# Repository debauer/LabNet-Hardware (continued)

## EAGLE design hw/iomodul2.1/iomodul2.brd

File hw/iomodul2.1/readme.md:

# Node V2.1

### V2.0 10'14 artwork by  
Sarah, Fablab KA  
Florolf, Entropia KA  

### V2.1 03'15 mod by
David Bauer, FabLab KA

- Hühnerfutter size changed from 0604 to 0805
- added and moved the LEDs
- changed JTAG/SWD connector layout to fit ti the STM SWD

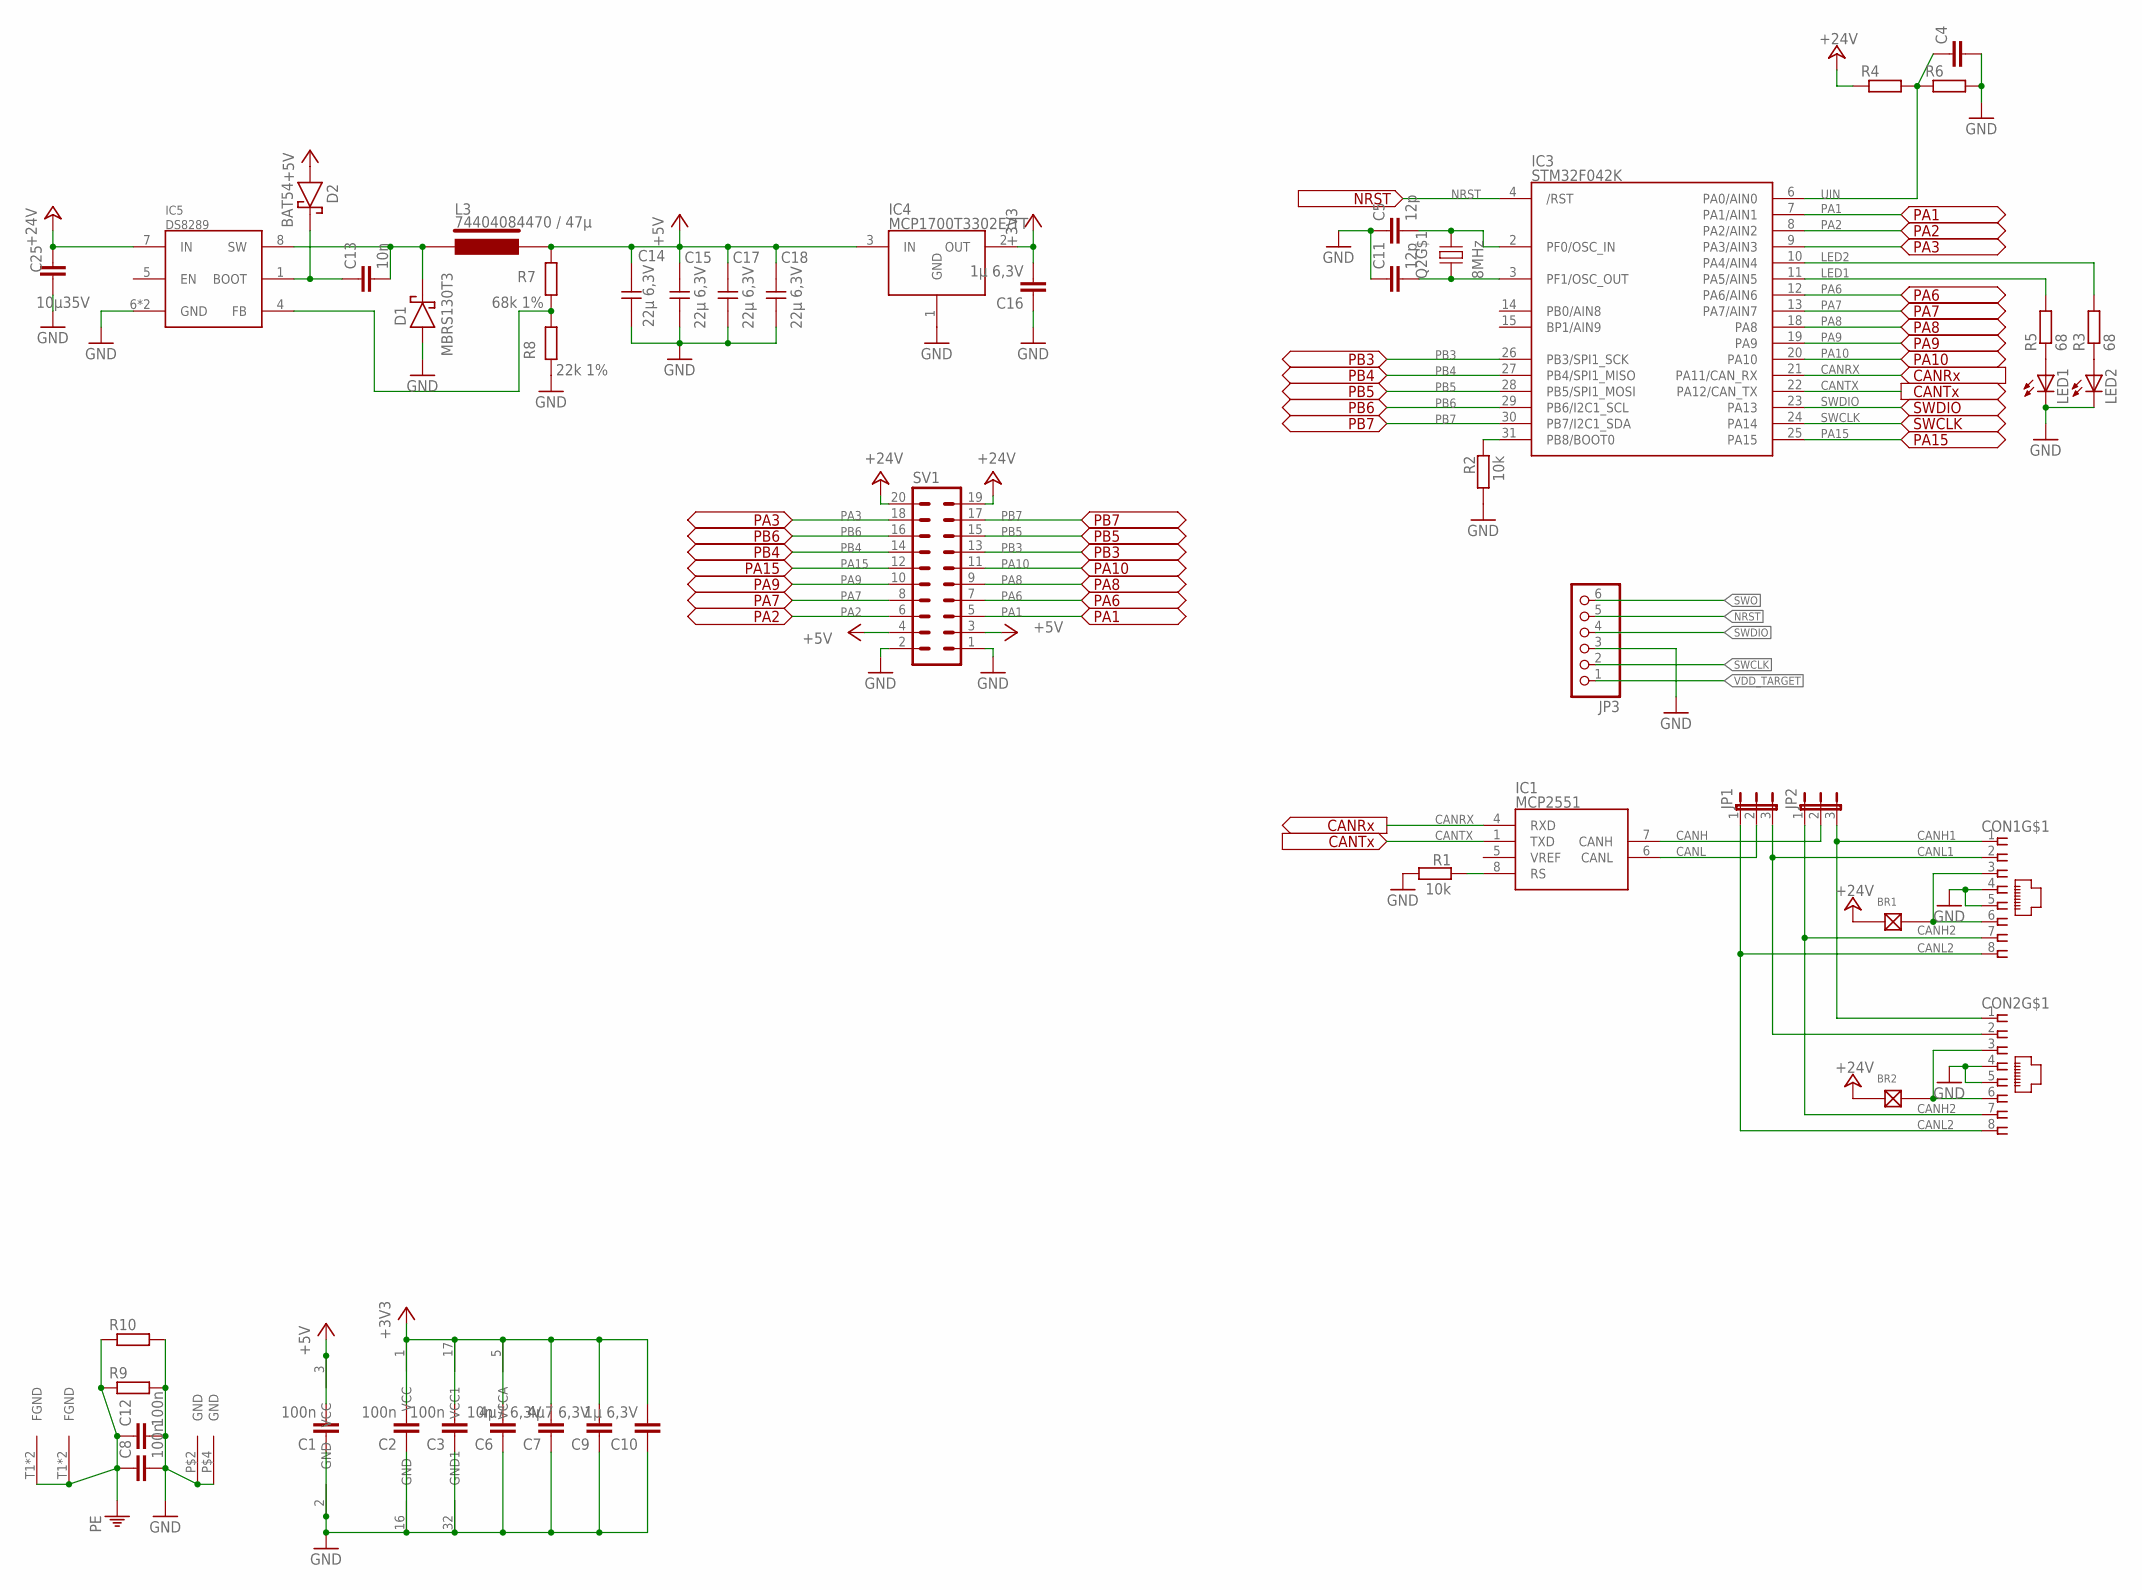
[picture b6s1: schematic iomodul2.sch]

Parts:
BR1, BR2: LÖTBRÜCKE-S; LÖTBRÜCKE
C1, C2, C3, C8, C12: 100n; C1206
C4: C-EUC1206; C1206
C5, C11: 12p; C1206
C6, C13: 10n; C1206
C7, C9: 4µ7 6,3V; C1206
C10, C16: 1µ 6,3V; C1206
C14, C15, C17, C18: 22µ 6,3V; 1210
C25: 10µ35V; C1206
CON1, CON2: MEBP_8-8G; MEBP
D1: MBRS130T3; SMB
D2: BAT54; SOT23/32
IC1: MCP2551; SO-8
IC3: STM32F042K; LQFP32
IC4: MCP1700T3302E/TT; SOT23
IC5: DS8289; SO8-POWERPAD
JP1, JP2: JP2E; JP2
JP3: PINHD-1X6; 1X06
L3: 74404084470 / 47µ; WE-LQS
LED1, LED2: LEDCHIPLED_0603; CHIPLED_0603
Q2: 8MHz; MT-CRYSTAL
R1, R2: 10k; R1206
R3, R5: 68; R1206
R4, R6, R9, R10: R-EU_R1206; R1206
R7: 68k 1%; R1206
R8: 22k 1%; R1206
SV1: MA10-2

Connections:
+3V3: C2.2, C3.2, C6.2, C7.2, C9.2, C10.2, C16.2, IC3.1 (VCC), IC3.5 (VCCA), IC3.17 (VCC1), IC4.2 (OUT)
+5V: C1.2, C14.2, C15.2, C17.2, C18.2, D2.1 (A), IC1.3 (VCC), IC4.3 (IN), L3.P$2, R7.2, SV1.3, SV1.4
+24V: BR1.1, BR2.1, C25.2, IC5.7 (IN), R4.1, SV1.19, SV1.20
CANH: IC1.7 (CANH), JP2.2
CANH1: CON1.1, CON2.1, JP2.3
CANH2: CON1.7, CON2.7, JP2.1
CANL: IC1.6 (CANL), JP1.2
CANL1: CON1.2, CON2.2, JP1.3
CANL2: CON1.8, CON2.8, JP1.1
CANRX: IC1.4 (RXD), IC3.21 (PA11/CAN_RX)
CANTX: IC1.1 (TXD), IC3.22 (PA12/CAN_TX)
GND: C1.1, C2.1, C3.1, C4.2, C5.1, C6.1, C7.1, C8.2, C9.1, C10.1, C11.1, C12.2, C14.1, C15.1, C16.1, C17.1, C18.1, C25.1, CON1.4, CON1.5, CON2.4, CON2.5, D1.A, IC1.2 (GND), IC3.16 (GND), IC3.32 (GND1), IC4.1 (GND), IC5.6 (GND), IC5.TP (GND), JP3.3, LED1.C, LED2.C, Q2.P$2 (GND), Q2.P$4 (GND), R1.2, R2.2, R6.2, R8.1, R9.2, R10.2, SV1.1, SV1.2
LED1: IC3.11 (PA5/AIN5), R5.2
LED2: IC3.10 (PA4/AIN4), R3.2
unnamed: IC1.8 (RS), R1.1
unnamed: BR1.2, CON1.3, CON1.6
unnamed: LED2.A, R3.1
unnamed: C11.2, IC3.3 (PF1/OSC_OUT), Q2.P$1 (1)
unnamed: C5.2, IC3.2 (PF0/OSC_IN), Q2.P$3 (2)
unnamed: BR2.2, CON2.3, CON2.6
unnamed: LED1.A, R5.1
unnamed: C13.1, D2.3 (K), IC5.1 (BOOT)
unnamed: C13.2, D1.K, IC5.8 (SW), L3.P$1
unnamed: IC3.31 (PB8/BOOT0), R2.1
unnamed: IC5.4 (FB), R7.1, R8.2
NRST: IC3.4 (/RST), JP3.5
PA1: IC3.7 (PA1/AIN1), SV1.5
PA2: IC3.8 (PA2/AIN2), SV1.6
PA3: IC3.9 (PA3/AIN3), SV1.18
PA6: IC3.12 (PA6/AIN6), SV1.7
PA7: IC3.13 (PA7/AIN7), SV1.8
PA8: IC3.18 (PA8), SV1.9
PA9: IC3.19 (PA9), SV1.10
PA10: IC3.20 (PA10), SV1.11
PA15: IC3.25 (PA15), SV1.12
PB3: IC3.26 (PB3/SPI1_SCK), SV1.13
PB4: IC3.27 (PB4/SPI1_MISO), SV1.14
PB5: IC3.28 (PB5/SPI1_MOSI), SV1.15
PB6: IC3.29 (PB6/I2C1_SCL), SV1.16
PB7: IC3.30 (PB7/I2C1_SDA), SV1.17
PE: C8.1, C12.1, CON1.T1 (FGND), CON1.T2 (FGND), CON2.T1 (FGND), CON2.T2 (FGND), R9.1, R10.1
SWCLK: IC3.24 (PA14), JP3.2
SWDIO: IC3.23 (PA13), JP3.4
SWO: JP3.6
UIN: C4.1, IC3.6 (PA0/AIN0), R4.2, R6.1
VDD_TARGET: JP3.1

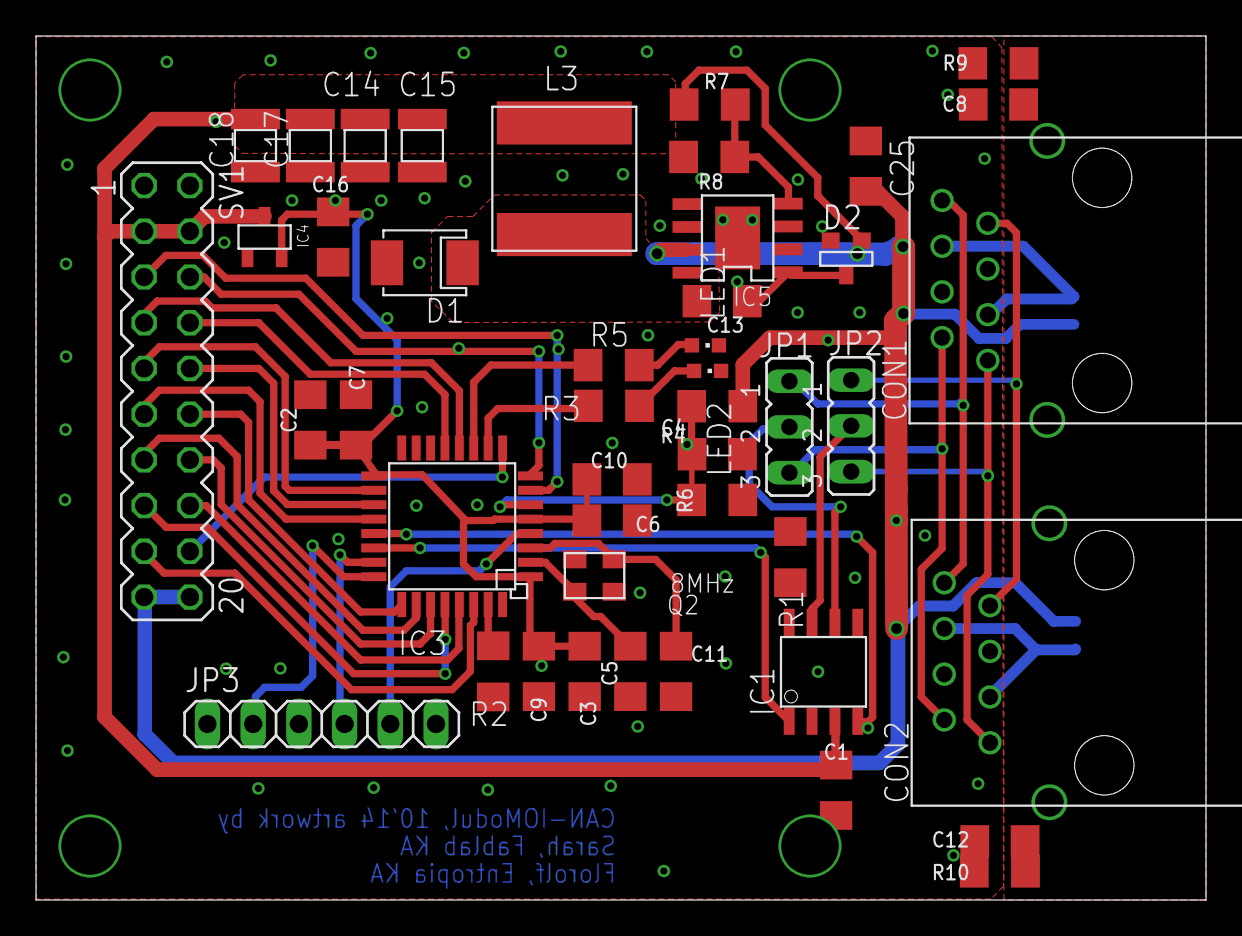
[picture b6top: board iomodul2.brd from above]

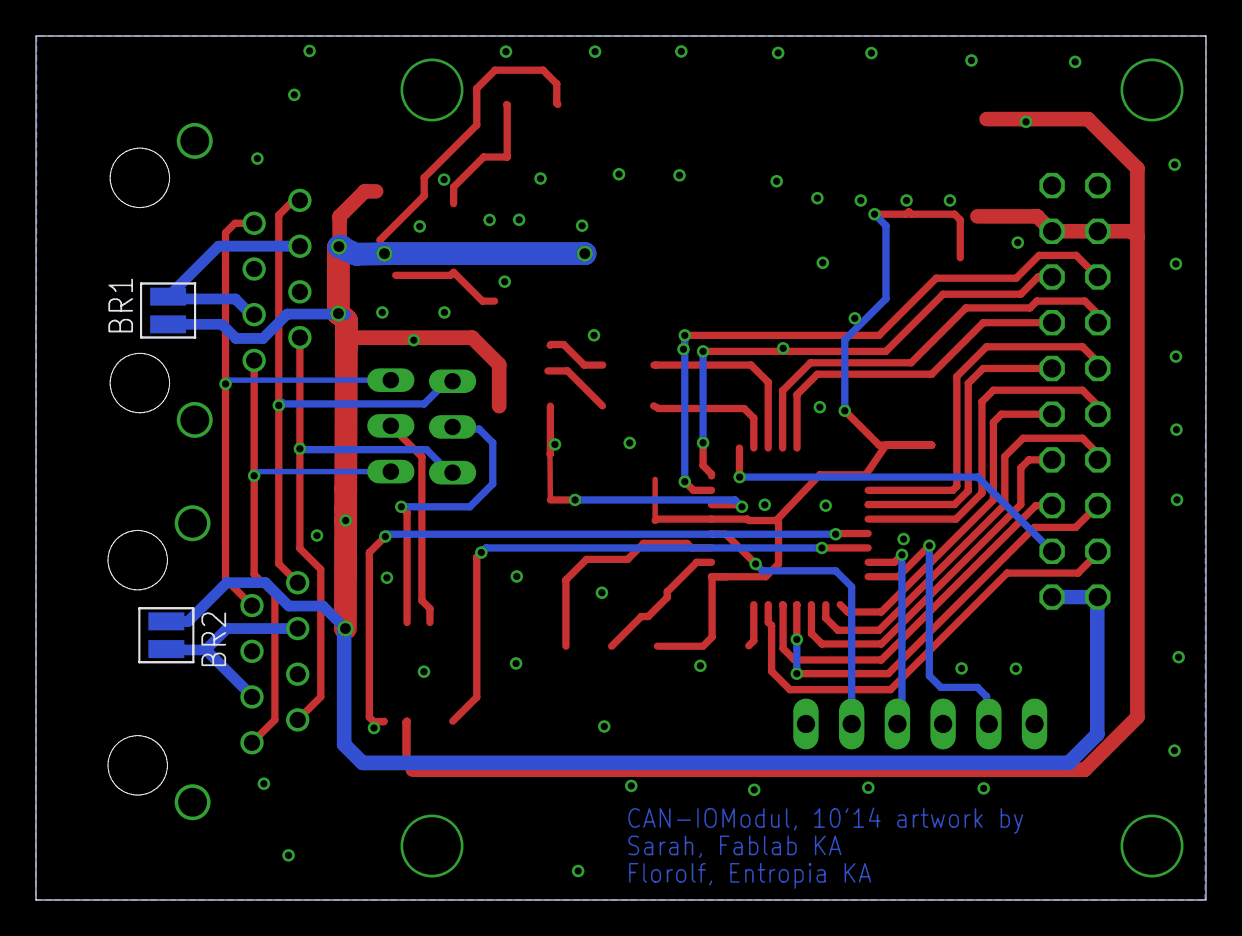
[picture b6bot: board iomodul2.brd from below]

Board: 2 copper layers, 65.0 x 48.0 mm, 47 parts (2 on the bottom side), 44 nets.

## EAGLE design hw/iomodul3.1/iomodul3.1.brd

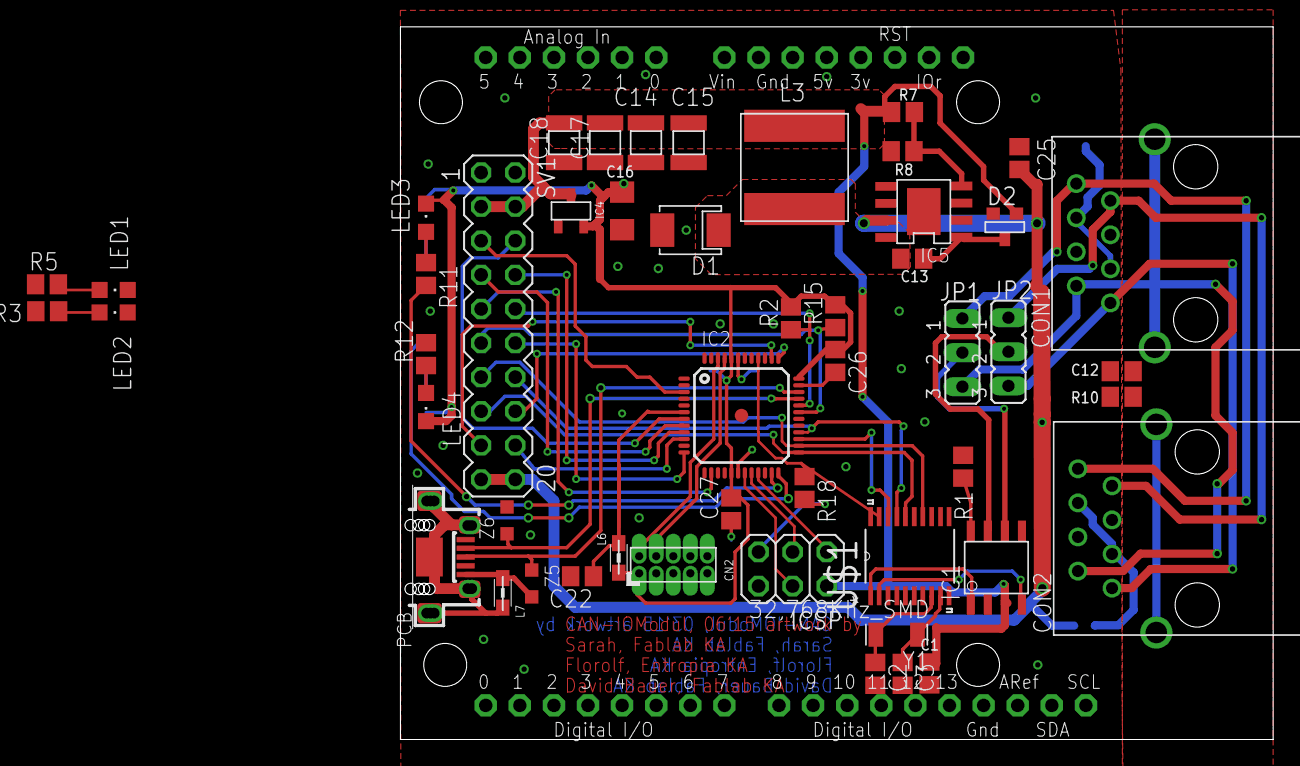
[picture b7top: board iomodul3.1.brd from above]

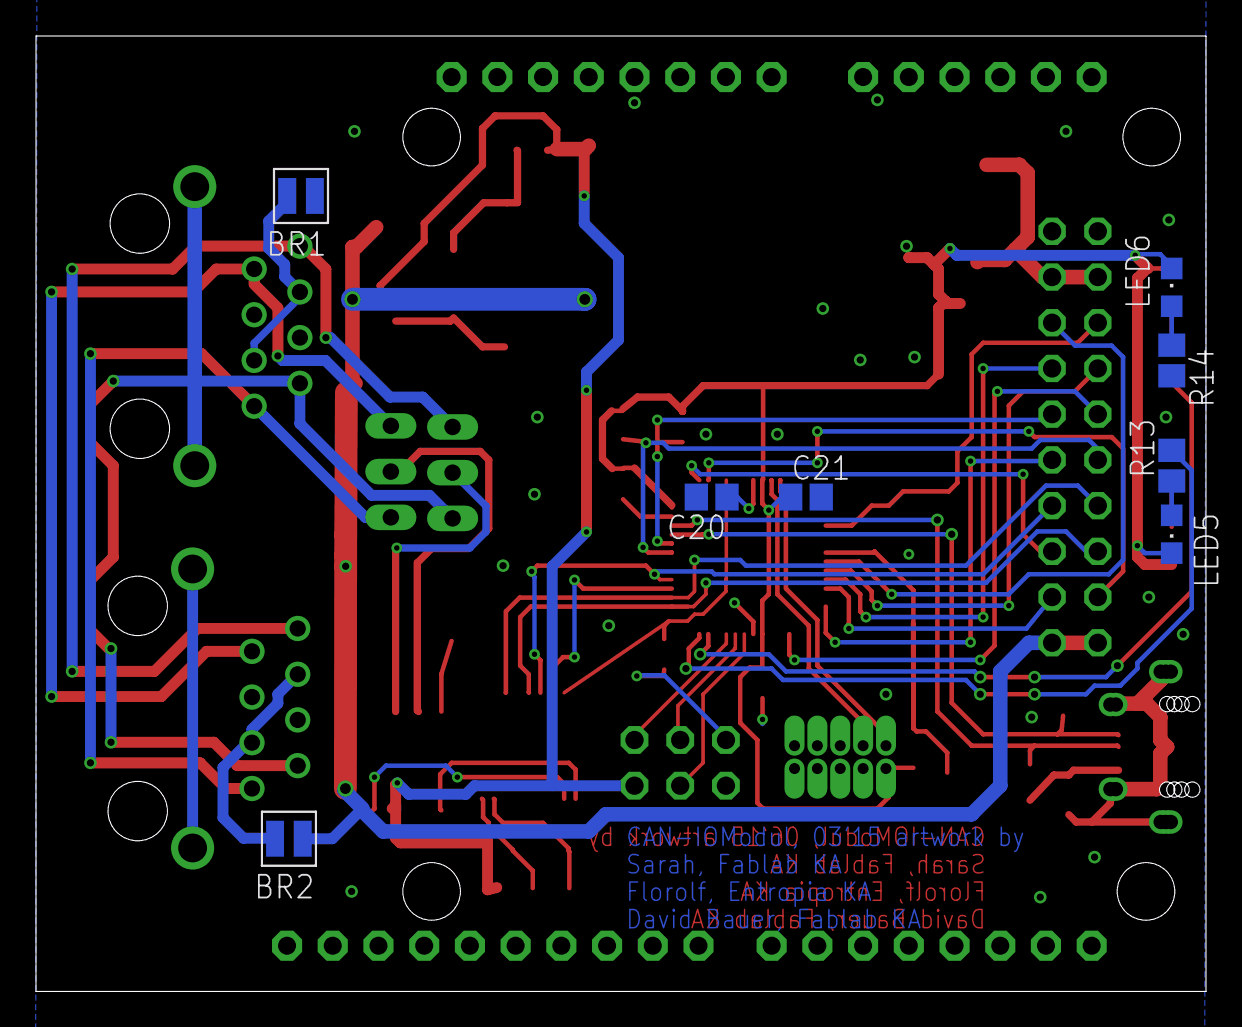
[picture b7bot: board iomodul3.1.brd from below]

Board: 2 copper layers, 65.0 x 53.1 mm, 59 parts (8 on the bottom side), 56 nets.

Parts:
BR1, BR2: LÖTBRÜCKE-S; LÖTBRÜCKE
C1, C12: 100n; C0805
C2, C3: 22p; C0805
C13: 10n; C0805
C14, C15, C17, C18: 22µ 6,3V; 1210
C16: 1µ 6,3V; C1206
C20: 1uF; C0805
C21, C22, C26, C27: 100nF; C0805
C25: 10µ35V; C0805
CN2: PINHEAD-2x5-P1.27; PINHEAD-2X5-P127
CON1, CON2: MEBP
D1: MBRS130T3; SMB
D2: BAT54; SOT23/32
IC1: MCP2551; SO-8
IC2: SAMD21G18A-AUT; TQFP48-7X7
IC4: MCP1700T3302E/TT; SOT23
IC5: DS8289; SO8-POWERPAD
ICSP: 3x2 M; 2X03
JP1, JP2: JP2
L3: 74404084470 / 47µ; WE-LQS
L6, L7: MH2029-300Y; 0805
LED1, LED2, LED3, LED4, LED5, LED6: CHIPLED_0805
R1, R2, R15: 10k; R0805
R3, R5, R11, R12, R13, R14: 68; R0805
R7: 68k 1%; R0805
R8: 22k 1%; R0805
R10: R0805
R18: 330R; R0805
SV1: MA10-2
U1: ARDUINOR3-DIMENSION; ARDUINOR3
U$1: MCP2515-I/ST; SOP65P640X110-20N
USB2: MICRO-USB-AB1; MCR-AB1-S-RA-SMT
Y1: 32,768Khz_SMD; RESONATOR_EPSON_FC_145
Z5, Z6: CG0603MLC-05E; CT/CN0603

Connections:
#0_RX: IC2.38, SV1.17, U1.D0
#1_TX: IC2.37, SV1.16, U1.D1
#3_IO: IC2.14, SV1.9
#5_LED1: IC2.24, R12.2, R13.2
#6_LED2: IC2.23, R11.2, R14.2
#9_CS_HEADER: IC2.12, SV1.12, U1.D9
#11_MOSI: IC2.25, SV1.15, U1.D11, U$1.16
#12_MISO: IC2.28, SV1.14, U1.D12, U$1.17
#13_SCK: IC2.26, SV1.13, U1.D10, U1.D13, U$1.14
#A0: IC2.3, SV1.5, U1.A0
#A1: IC2.7, SV1.6, U1.A1
#A2: IC2.8, SV1.7, U1.A2
#A3: IC2.9, SV1.8, U1.A3
#A4: IC2.10, SV1.18
+3V3: C16.2, C21.1, C26.1, C27.2, CN2.1, IC2.17, IC2.36, IC2.44, IC4.2, L6.2, LED3.C, LED4.C, LED5.C, LED6.C, R2.2, R15.2, U1.3V, U1.IOREF
+5V: C1.2, C14.2, C15.2, C17.2, C18.2, D2.1, IC1.3, IC4.3, ICSP.2, L3.P$2, R7.2, SV1.3, SV1.4, U1.5V
+24V: BR1.1, BR2.1, C25.2, IC5.7, SV1.19, SV1.20, U1.VIN
CANH: IC1.7, JP2.2
CANH1: CON1.1, CON2.1, JP2.3
CANH2: CON1.7, CON2.7, JP2.1
CANL: IC1.6, JP1.2
CANL1: CON1.2, CON2.2, JP1.3
CANL2: CON1.8, CON2.8, JP1.1
CANRX: IC1.4, U$1.2
CANTX: IC1.1, U$1.1
CS_MCP: IC2.27, U$1.18
GND: C1.1, C2.2, C3.2, C12.2, C14.1, C15.1, C16.1, C17.1, C18.1, C20.2, C21.2, C22.2, C25.1, C26.2, C27.1, CN2.3, CN2.5, CN2.9, CON1.4, CON1.5, CON2.4, CON2.5, D1.A, IC1.2, IC2.5, IC2.18, IC2.35, IC2.42, IC4.1, IC5.6, IC5.TP, ICSP.6, L7.2, LED1.C, LED2.C, R1.2, R8.1, R10.2, SV1.1, SV1.2, U1.GND, U1.GND1, U1.GND2, USB2.5, Z5.2, Z6.2
MCPOSC1: C3.1, U$1.9, Y1.P$1
MCPOSC2: C2.1, U$1.8, Y1.P$2
unnamed: IC1.8, R1.1
unnamed: BR1.2, CON1.3, CON1.6
unnamed: LED2.A, R3.1
unnamed: L7.1, USB2.P$1, USB2.P$2, USB2.P$3, USB2.P$4, USB2.P$5, USB2.P$6, USB2.P$7, USB2.P$8, USB2.P$9, USB2.P$10, USB2.P$11, USB2.S1, USB2.S2, USB2.S3, USB2.S4
unnamed: BR2.2, CON2.3, CON2.6
unnamed: LED1.A, R5.1
unnamed: LED5.A, R13.1
unnamed: LED6.A, R14.1
unnamed: LED4.A, R12.1
unnamed: LED3.A, R11.1
unnamed: C13.1, D2.3, IC5.1
unnamed: C13.2, D1.K, IC5.8, L3.P$1
unnamed: C22.1, IC2.6, L6.1
unnamed: IC5.4, R7.1, R8.2
PA30_SWCLK: CN2.4, IC2.45
PA31_SWDIO1: CN2.2, IC2.46
PB10_S4_SPI_MOSI: IC2.19, ICSP.4
PB11_S4_SPI_SCK: IC2.20, ICSP.3
PB12_S4_SPI_MISO: IC2.21, ICSP.1
PE: C12.1, CON1.T1, CON1.T2, CON2.T1, CON2.T2, R10.1
RESET: CN2.10, ICSP.5, R18.2
SCL: IC2.32, R2.1, SV1.10, U1.SCL
SDA: IC2.31, R15.1, SV1.11, U1.SDA
TARGET_RESET_EDBG: IC2.40, R18.1, U1.RESET, U$1.19
TARGET_USB_N: IC2.33, USB2.2, Z6.1
TARGET_USB_P: IC2.34, USB2.3, Z5.1
VDDCORE: C20.1, IC2.43
